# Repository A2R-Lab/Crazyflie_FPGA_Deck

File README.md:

# Deck_FPGA

This repository documents the design of an FPGA-based expansion board for the Crazyflie drone platform, featuring an AMD Xilinx Artix-7 100T FPGA and developed in KiCad.

The board was developed to support the acceleration of linear Model Predictive Control (MPC) execution onboard the Crazyflie quadrotor platform.

## Repository Contents

- `Deck_FPGA.kicad_sch`: KiCad schematic
- `Deck_FPGA.kicad_pcb`: KiCad PCB layout
- `Deck_FPGA.kicad_pro`: KiCad project file
- `Deck_FPGA.pdf`: exported board documentation
- `plot/`: fabrication outputs / Gerbers

## Inspiration

This project was inspired by the board presented in *FPGA-Based Neural Thrust Controller for UAVs* by Sharif Azem, David Scheunert, Mengguang Li, Jonas Gehrunger, Kai Cui, Christian Hochberger, and Heinz Koeppl (2024).

## Related Components

- FPGA accelerator implementation: `ADMM_FPGA`
- Crazyflie firmware integration: `crazyflie_fpga_firmware`

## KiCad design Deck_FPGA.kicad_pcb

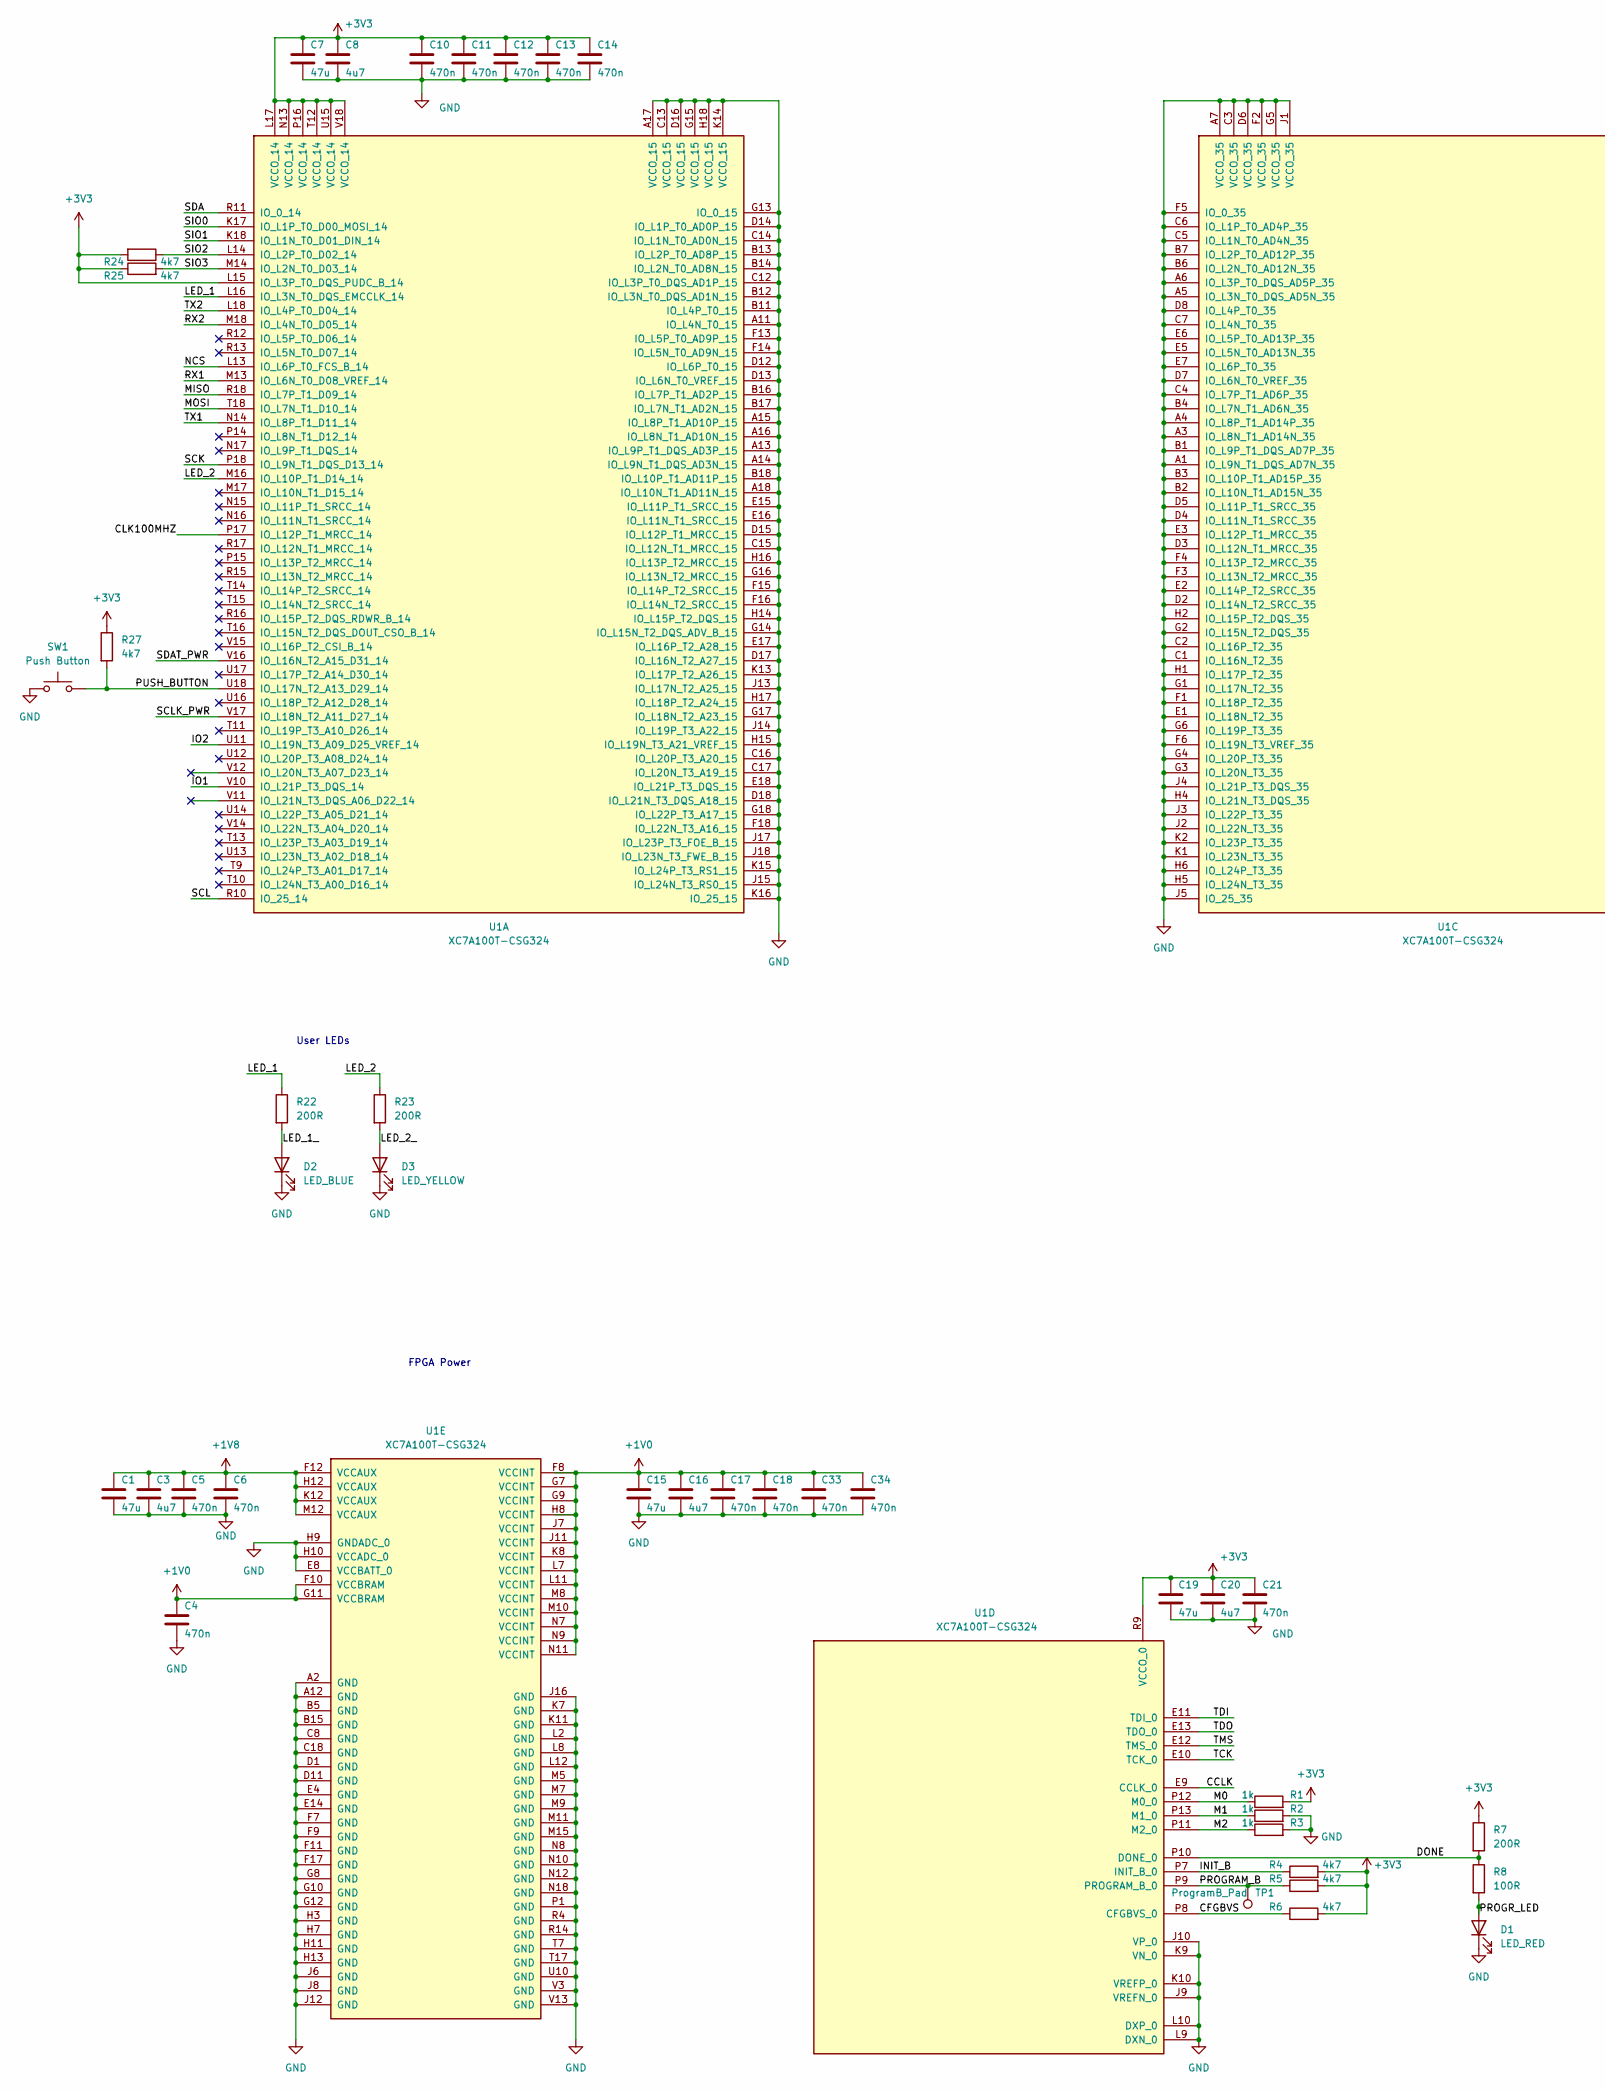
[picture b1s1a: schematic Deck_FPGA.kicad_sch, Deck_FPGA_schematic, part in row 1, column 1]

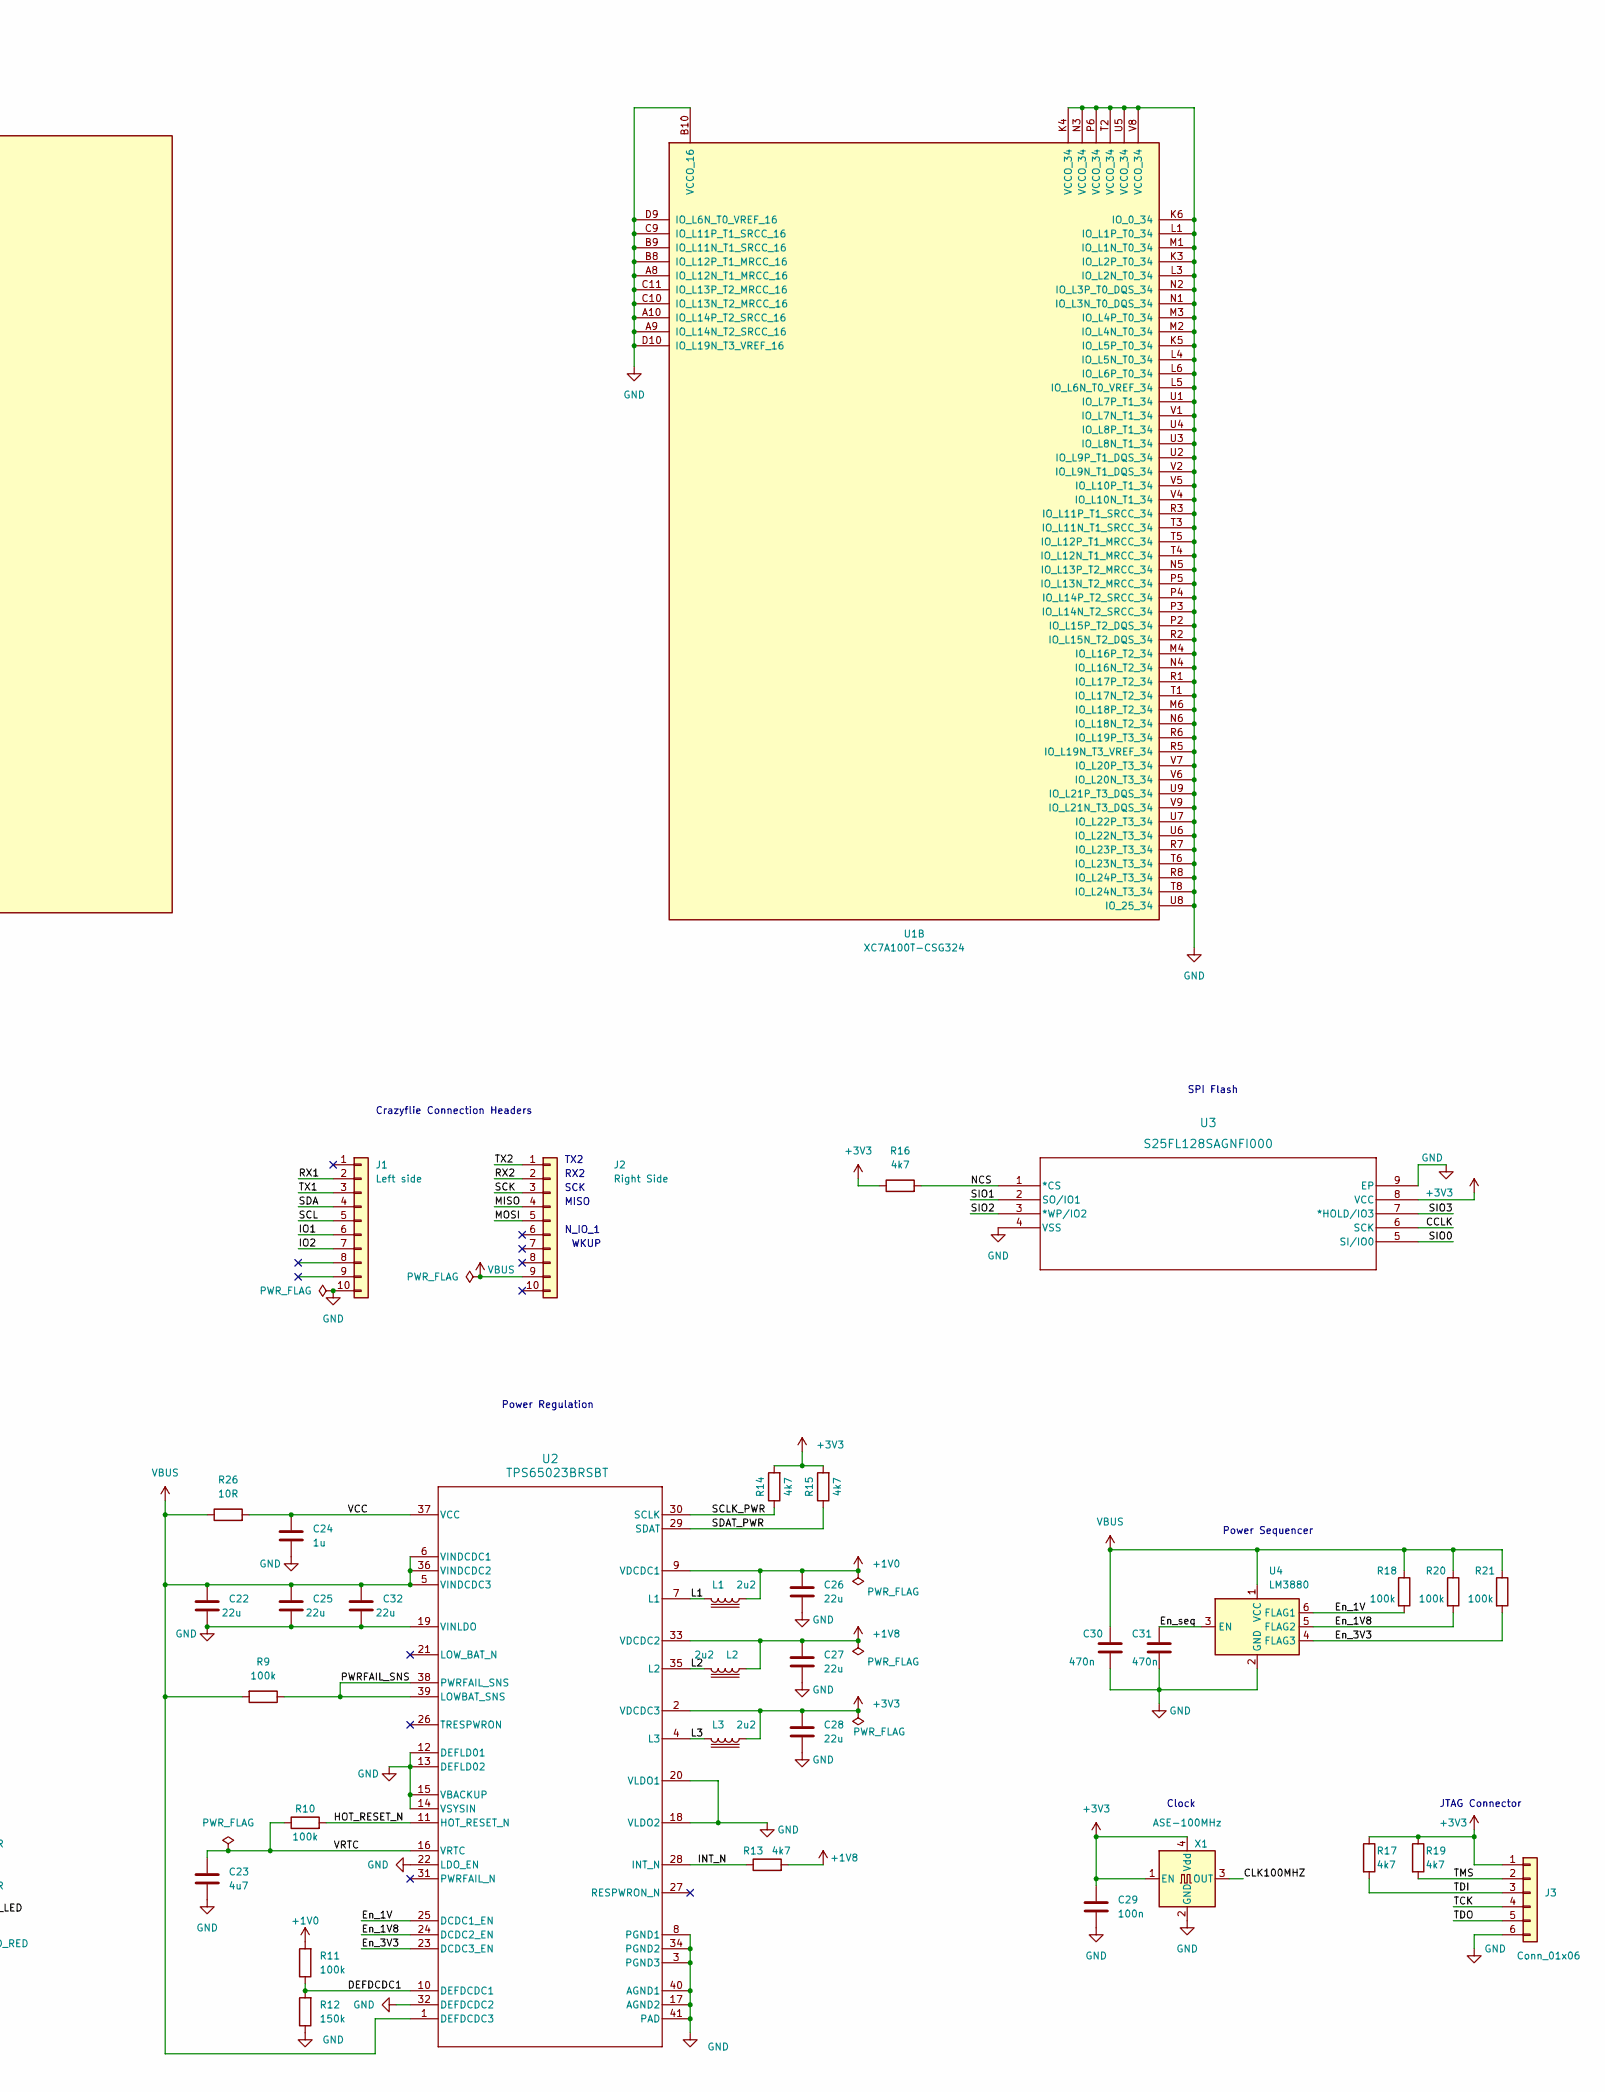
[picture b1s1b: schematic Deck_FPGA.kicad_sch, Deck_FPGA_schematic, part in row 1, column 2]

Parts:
C1: 47u; C_0603_1608Metric; LCSC C140782
C3, C16: 4u7; C_0402_1005Metric; LCSC C23733
C4: 470n; C_0402_1005Metric; LCSC C106255
C5, C6, C10, C11, C12, C13, C14, C17, C18, C21, C30, C31, C33, C34: 470n; C_0402_1005Metric
C7, C15, C19: 47u; C_0603_1608Metric
C8, C20, C23: 4u7; C_0402_1005Metric
C22, C25: 22u; C_0603_1608Metric; LCSC C86295
C24: 1u; C_0603_1608Metric; LCSC C15849
C26, C27, C28, C32: 22u; C_0603_1608Metric
C29: 100n; C_0402_1005Metric; LCSC C60474
D1: LED_RED; LED_0603_1608Metric; LCSC C5879214
D2: LED_BLUE; LED_0603_1608Metric; LCSC C5879217
D3: LED_YELLOW; LED_0603_1608Metric; LCSC C5879216
J1: Left side; BF090-10-X-B2
J2: Right Side; BF090-10-X-B2
J3: Conn_01x06; PinHeader_1x06_P2.54mm_Vertical
L1: 2u2; IND_WE-PMCI_0806_WRE; LCSC C71386
L2, L3: 2u2; IND_WE-PMCI_0806_WRE
R1: 1k; R_0402_1005Metric; LCSC C11702
R2, R3: 1k; R_0402_1005Metric
R4: 4k7; R_0402_1005Metric; LCSC C25900
R5, R6, R13, R14, R15, R16, R17, R19, R24, R25, R27: 4k7; R_0402_1005Metric
R7: 200R; R_0402_1005Metric; LCSC C25087
R8: 100R; R_0402_1005Metric; LCSC C25076
R9: 100k; R_0402_1005Metric; LCSC C2906859
R10, R11, R18, R20, R21: 100k; R_0402_1005Metric
R12: 150k; R_0402_1005Metric; LCSC C2909320
R22, R23: 200R; R_0402_1005Metric
R26: 10R; R_0402_1005Metric; LCSC C413044
SW1: Push Button; SW_EVQ-P3401P; LCSC C79163
TP1: ProgramB_Pad; TestPoint_Pad_D1.0mm
U1: XC7A100T-CSG324; Xilinx_CSG324; LCSC C5181214
U2: TPS65023BRSBT; RSB0040B; LCSC C138723
U3: S25FL128SAGNFI000; WNG008_SPA; LCSC C22445046
U4: LM3880; SOT-23-6; LCSC C2650186
X1: ASE-100MHz; Oscillator_SMD_Abracon_ASE-4Pin_3.2x2.5mm; LCSC C596959

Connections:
+1V0: C4.1, C15.1, C16.1, C17.1, C18.1, C26.1, C33.1, C34.1, L1.1, R11.2, U1.F8 (VCCINT), U1.F10 (VCCBRAM), U1.G7 (VCCINT), U1.G9 (VCCINT), U1.G11 (VCCBRAM), U1.H8 (VCCINT), U1.J7 (VCCINT), U1.J11 (VCCINT), U1.K8 (VCCINT), U1.L7 (VCCINT), U1.L11 (VCCINT), U1.M8 (VCCINT), U1.M10 (VCCINT), U1.N7 (VCCINT), U1.N9 (VCCINT), U1.N11 (VCCINT), U2.9 (VDCDC1)
+1V8: C1.1, C3.1, C5.1, C6.1, C27.1, L2.2, R13.2, U1.F12 (VCCAUX), U1.H12 (VCCAUX), U1.K12 (VCCAUX), U1.M12 (VCCAUX), U2.33 (VDCDC2)
+3V3: C7.1, C8.1, C10.1, C11.1, C12.1, C13.1, C14.1, C19.1, C20.1, C21.1, C28.1, C29.1, J3.1, L3.1, R1.2, R4.2, R5.2, R6.2, R7.1, R14.2, R15.2, R16.1, R17.1, R19.1, R24.2, R25.1, R27.1, U1.L15 (IO_L3P_T0_DQS_PUDC_B_14), U1.L17 (VCCO_14), U1.N13 (VCCO_14), U1.P16 (VCCO_14), U1.R9 (VCCO_0), U1.T12 (VCCO_14), U1.U15 (VCCO_14), U1.V18 (VCCO_14), U2.2 (VDCDC3), U3.8 (VCC), X1.1 (EN), X1.4 (Vdd)
/CCLK: U1.E9 (CCLK_0), U3.6 (SCK)
/CFGBVS: R6.1, U1.P8 (CFGBVS_0)
/CLK100MHZ: U1.P17 (IO_L12P_T1_MRCC_14), X1.3 (OUT)
/DEFDCDC1: R11.1, R12.2, U2.10 (DEFDCDC1)
/DONE: R7.2, R8.1, U1.P10 (DONE_0)
/En_1V: R18.2, U2.25 (DCDC1_EN), U4.6 (FLAG1)
/En_1V8: R20.2, U2.24 (DCDC2_EN), U4.5 (FLAG2)
/En_3V3: R21.2, U2.23 (DCDC3_EN), U4.4 (FLAG3)
/En_seq: C31.1, U4.3 (EN)
/HOT_RESET_N: R10.2, U2.11 (HOT_RESET_N)
/INIT_B: R4.1, U1.P7 (INIT_B_0)
/INT_N: R13.1, U2.28 (INT_N)
/IO1: J1.6, U1.V10 (IO_L21P_T3_DQS_14)
/IO2: J1.7, U1.U11 (IO_L19N_T3_A09_D25_VREF_14)
/L1: L1.2, U2.7 (L1)
/L2: L2.1, U2.35 (L2)
/L3: L3.2, U2.4 (L3)
/LED_1: R22.1, U1.L16 (IO_L3N_T0_DQS_EMCCLK_14)
/LED_1_: D2.2 (A), R22.2
/LED_2: R23.1, U1.M16 (IO_L10P_T1_D14_14)
/LED_2_: D3.2 (A), R23.2
/M0: R1.1, U1.P12 (M0_0)
/M1: R2.1, U1.P13 (M1_0)
/M2: R3.1, U1.P11 (M2_0)
/MISO: J2.4, U1.R18 (IO_L7P_T1_D09_14)
/MOSI: J2.5, U1.T18 (IO_L7N_T1_D10_14)
/NCS: R16.2, U1.L13 (IO_L6P_T0_FCS_B_14), U3.1 (*CS)
/PROGRAM_B: R5.1, TP1.1, U1.P9 (PROGRAM_B_0)
/PROGR_LED: D1.2 (A), R8.2
/PUSH_BUTTON: R27.2, SW1.2, U1.U18 (IO_L17N_T2_A13_D29_14)
/PWRFAIL_SNS: R9.1, U2.38 (PWRFAIL_SNS), U2.39 (LOWBAT_SNS)
/RX1: J1.2, U1.M13 (IO_L6N_T0_D08_VREF_14)
/RX2: J2.2, U1.M18 (IO_L4N_T0_D05_14)
/SCK: J2.3, U1.P18 (IO_L9N_T1_DQS_D13_14)
/SCL: J1.5, U1.R10 (IO_25_14)
/SCLK_PWR: R14.1, U1.V17 (IO_L18N_T2_A11_D27_14), U2.30 (SCLK)
/SDA: J1.4, U1.R11 (IO_0_14)
/SDAT_PWR: R15.1, U1.V16 (IO_L16N_T2_A15_D31_14), U2.29 (SDAT)
/SIO0: U1.K17 (IO_L1P_T0_D00_MOSI_14), U3.5 (SI/IO0)
/SIO1: U1.K18 (IO_L1N_T0_D01_DIN_14), U3.2 (SO/IO1)
/SIO2: R24.1, U1.L14 (IO_L2P_T0_D02_14), U3.3 (*WP/IO2)
/SIO3: R25.2, U1.M14 (IO_L2N_T0_D03_14), U3.7 (*HOLD/IO3)
/TCK: J3.4, U1.E10 (TCK_0)
/TDI: J3.3, R17.2, U1.E11 (TDI_0)
/TDO: J3.5, U1.E13 (TDO_0)
/TMS: J3.2, R19.2, U1.E12 (TMS_0)
/TX1: J1.3, U1.N14 (IO_L8P_T1_D11_14)
/TX2: J2.1, U1.L18 (IO_L4P_T0_D04_14)
/VCC: C24.1, R26.2, U2.37 (VCC)
/VRTC: C23.1, R10.1, U2.16 (VRTC)
GND: C1.2, C3.2, C4.2, C5.2, C6.2, C7.2, C8.2, C10.2, C11.2, C12.2, C13.2, C14.2, C15.2, C16.2, C17.2, C18.2, C19.2, C20.2, C21.2, C22.2, C23.2, C24.2, C25.2, C26.2, C27.2, C28.2, C29.2, C30.2, C31.2, C32.2, C33.2, C34.2, D1.1 (K), D2.1 (K), D3.1 (K), J1.10, J3.6, R2.2, R3.2, R12.1, SW1.1, U1.A1 (IO_L9N_T1_DQS_AD7N_35), U1.A2 (GND), U1.A3 (IO_L8N_T1_AD14N_35), U1.A4 (IO_L8P_T1_AD14P_35), U1.A5 (IO_L3N_T0_DQS_AD5N_35), U1.A6 (IO_L3P_T0_DQS_AD5P_35), U1.A7 (VCCO_35), U1.A8 (IO_L12N_T1_MRCC_16), U1.A9 (IO_L14N_T2_SRCC_16), U1.A10 (IO_L14P_T2_SRCC_16), U1.A11 (IO_L4N_T0_15), U1.A12 (GND), U1.A13 (IO_L9P_T1_DQS_AD3P_15), U1.A14 (IO_L9N_T1_DQS_AD3N_15), U1.A15 (IO_L8P_T1_AD10P_15), U1.A16 (IO_L8N_T1_AD10N_15), U1.A17 (VCCO_15), U1.A18 (IO_L10N_T1_AD11N_15), U1.B1 (IO_L9P_T1_DQS_AD7P_35), U1.B2 (IO_L10N_T1_AD15N_35), U1.B3 (IO_L10P_T1_AD15P_35), U1.B4 (IO_L7N_T1_AD6N_35), U1.B5 (GND), U1.B6 (IO_L2N_T0_AD12N_35), U1.B7 (IO_L2P_T0_AD12P_35), U1.B8 (IO_L12P_T1_MRCC_16), U1.B9 (IO_L11N_T1_SRCC_16), U1.B10 (VCCO_16), U1.B11 (IO_L4P_T0_15), U1.B12 (IO_L3N_T0_DQS_AD1N_15), U1.B13 (IO_L2P_T0_AD8P_15), U1.B14 (IO_L2N_T0_AD8N_15), U1.B15 (GND), U1.B16 (IO_L7P_T1_AD2P_15), U1.B17 (IO_L7N_T1_AD2N_15), U1.B18 (IO_L10P_T1_AD11P_15), U1.C1 (IO_L16N_T2_35), U1.C2 (IO_L16P_T2_35), U1.C3 (VCCO_35), U1.C4 (IO_L7P_T1_AD6P_35), U1.C5 (IO_L1N_T0_AD4N_35), U1.C6 (IO_L1P_T0_AD4P_35), U1.C7 (IO_L4N_T0_35), U1.C8 (GND), U1.C9 (IO_L11P_T1_SRCC_16), U1.C10 (IO_L13N_T2_MRCC_16), U1.C11 (IO_L13P_T2_MRCC_16), U1.C12 (IO_L3P_T0_DQS_AD1P_15), U1.C13 (VCCO_15), U1.C14 (IO_L1N_T0_AD0N_15), U1.C15 (IO_L12N_T1_MRCC_15), U1.C16 (IO_L20P_T3_A20_15), U1.C17 (IO_L20N_T3_A19_15), U1.C18 (GND), U1.D1 (GND), U1.D2 (IO_L14N_T2_SRCC_35), U1.D3 (IO_L12N_T1_MRCC_35), U1.D4 (IO_L11N_T1_SRCC_35), U1.D5 (IO_L11P_T1_SRCC_35), U1.D6 (VCCO_35), U1.D7 (IO_L6N_T0_VREF_35), U1.D8 (IO_L4P_T0_35), U1.D9 (IO_L6N_T0_VREF_16), U1.D10 (IO_L19N_T3_VREF_16), U1.D11 (GND), U1.D12 (IO_L6P_T0_15), U1.D13 (IO_L6N_T0_VREF_15), U1.D14 (IO_L1P_T0_AD0P_15), U1.D15 (IO_L12P_T1_MRCC_15), U1.D16 (VCCO_15), U1.D17 (IO_L16N_T2_A27_15), U1.D18 (IO_L21N_T3_DQS_A18_15), U1.E1 (IO_L18N_T2_35), U1.E2 (IO_L14P_T2_SRCC_35), U1.E3 (IO_L12P_T1_MRCC_35), U1.E4 (GND), U1.E5 (IO_L5N_T0_AD13N_35), U1.E6 (IO_L5P_T0_AD13P_35), U1.E7 (IO_L6P_T0_35), U1.E8 (VCCBATT_0), U1.E14 (GND), U1.E15 (IO_L11P_T1_SRCC_15), U1.E16 (IO_L11N_T1_SRCC_15), U1.E17 (IO_L16P_T2_A28_15), U1.E18 (IO_L21P_T3_DQS_15), U1.F1 (IO_L18P_T2_35), U1.F2 (VCCO_35), U1.F3 (IO_L13N_T2_MRCC_35), U1.F4 (IO_L13P_T2_MRCC_35), U1.F5 (IO_0_35), U1.F6 (IO_L19N_T3_VREF_35), U1.F7 (GND), U1.F9 (GND), U1.F11 (GND), U1.F13 (IO_L5P_T0_AD9P_15), U1.F14 (IO_L5N_T0_AD9N_15), U1.F15 (IO_L14P_T2_SRCC_15), U1.F16 (IO_L14N_T2_SRCC_15), U1.F17 (GND), U1.F18 (IO_L22N_T3_A16_15), U1.G1 (IO_L17N_T2_35), U1.G2 (IO_L15N_T2_DQS_35), U1.G3 (IO_L20N_T3_35), U1.G4 (IO_L20P_T3_35), U1.G5 (VCCO_35), U1.G6 (IO_L19P_T3_35), U1.G8 (GND), U1.G10 (GND), U1.G12 (GND), U1.G13 (IO_0_15), U1.G14 (IO_L15N_T2_DQS_ADV_B_15), U1.G15 (VCCO_15), U1.G16 (IO_L13N_T2_MRCC_15), U1.G17 (IO_L18N_T2_A23_15), U1.G18 (IO_L22P_T3_A17_15), U1.H1 (IO_L17P_T2_35), U1.H2 (IO_L15P_T2_DQS_35), U1.H3 (GND), U1.H4 (IO_L21N_T3_DQS_35), U1.H5 (IO_L24N_T3_35), U1.H6 (IO_L24P_T3_35), U1.H7 (GND), U1.H9 (GNDADC_0), U1.H10 (VCCADC_0), U1.H11 (GND), U1.H13 (GND), U1.H14 (IO_L15P_T2_DQS_15), U1.H15 (IO_L19N_T3_A21_VREF_15), U1.H16 (IO_L13P_T2_MRCC_15), U1.H17 (IO_L18P_T2_A24_15), U1.H18 (VCCO_15), U1.J1 (VCCO_35), U1.J2 (IO_L22N_T3_35), U1.J3 (IO_L22P_T3_35), U1.J4 (IO_L21P_T3_DQS_35), U1.J5 (IO_25_35), U1.J6 (GND), U1.J8 (GND), U1.J9 (VREFN_0), U1.J10 (VP_0), U1.J12 (GND), U1.J13 (IO_L17N_T2_A25_15), U1.J14 (IO_L19P_T3_A22_15), U1.J15 (IO_L24N_T3_RS0_15), U1.J16 (GND), U1.J17 (IO_L23P_T3_FOE_B_15), U1.J18 (IO_L23N_T3_FWE_B_15), U1.K1 (IO_L23N_T3_35), U1.K2 (IO_L23P_T3_35), U1.K3 (IO_L2P_T0_34), U1.K4 (VCCO_34), U1.K5 (IO_L5P_T0_34), U1.K6 (IO_0_34), U1.K7 (GND), U1.K9 (VN_0), U1.K10 (VREFP_0), U1.K11 (GND), U1.K13 (IO_L17P_T2_A26_15), U1.K14 (VCCO_15), U1.K15 (IO_L24P_T3_RS1_15), U1.K16 (IO_25_15), U1.L1 (IO_L1P_T0_34), U1.L2 (GND), U1.L3 (IO_L2N_T0_34), U1.L4 (IO_L5N_T0_34), U1.L5 (IO_L6N_T0_VREF_34), U1.L6 (IO_L6P_T0_34), U1.L8 (GND), U1.L9 (DXN_0), U1.L10 (DXP_0), U1.L12 (GND), U1.M1 (IO_L1N_T0_34), U1.M2 (IO_L4N_T0_34), U1.M3 (IO_L4P_T0_34), U1.M4 (IO_L16P_T2_34), U1.M5 (GND), U1.M6 (IO_L18P_T2_34), U1.M7 (GND), U1.M9 (GND), U1.M11 (GND), U1.M15 (GND), U1.N1 (IO_L3N_T0_DQS_34), U1.N2 (IO_L3P_T0_DQS_34), U1.N3 (VCCO_34), U1.N4 (IO_L16N_T2_34), U1.N5 (IO_L13P_T2_MRCC_34), U1.N6 (IO_L18N_T2_34), U1.N8 (GND), U1.N10 (GND), U1.N12 (GND), U1.N18 (GND), U1.P1 (GND), U1.P2 (IO_L15P_T2_DQS_34), U1.P3 (IO_L14N_T2_SRCC_34), U1.P4 (IO_L14P_T2_SRCC_34), U1.P5 (IO_L13N_T2_MRCC_34), U1.P6 (VCCO_34), U1.R1 (IO_L17P_T2_34), U1.R2 (IO_L15N_T2_DQS_34), U1.R3 (IO_L11P_T1_SRCC_34), U1.R4 (GND), U1.R5 (IO_L19N_T3_VREF_34), U1.R6 (IO_L19P_T3_34), U1.R7 (IO_L23P_T3_34), U1.R8 (IO_L24P_T3_34), U1.R14 (GND), U1.T1 (IO_L17N_T2_34), U1.T2 (VCCO_34), U1.T3 (IO_L11N_T1_SRCC_34), U1.T4 (IO_L12N_T1_MRCC_34), U1.T5 (IO_L12P_T1_MRCC_34), U1.T6 (IO_L23N_T3_34), U1.T7 (GND), U1.T8 (IO_L24N_T3_34), U1.T17 (GND), U1.U1 (IO_L7P_T1_34), U1.U2 (IO_L9P_T1_DQS_34), U1.U3 (IO_L8N_T1_34), U1.U4 (IO_L8P_T1_34), U1.U5 (VCCO_34), U1.U6 (IO_L22N_T3_34), U1.U7 (IO_L22P_T3_34), U1.U8 (IO_25_34), U1.U9 (IO_L21P_T3_DQS_34), U1.U10 (GND), U1.V1 (IO_L7N_T1_34), U1.V2 (IO_L9N_T1_DQS_34), U1.V3 (GND), U1.V4 (IO_L10N_T1_34), U1.V5 (IO_L10P_T1_34), U1.V6 (IO_L20N_T3_34), U1.V7 (IO_L20P_T3_34), U1.V8 (VCCO_34), U1.V9 (IO_L21N_T3_DQS_34), U1.V13 (GND), U2.3 (PGND3), U2.8 (PGND1), U2.12 (DEFLD01), U2.13 (DEFLD02), U2.14 (VSYSIN), U2.15 (VBACKUP), U2.17 (AGND2), U2.18 (VLDO2), U2.19 (VINLDO), U2.20 (VLDO1), U2.22 (LDO_EN), U2.32 (DEFDCDC2), U2.34 (PGND2), U2.40 (AGND1), U2.41 (PAD), U3.4 (VSS), U3.9 (EP), U4.2 (GND), X1.2 (GND)
VBUS: C22.1, C25.1, C30.1, C32.1, J2.9, R9.2, R18.1, R20.1, R21.1, R26.1, U2.1 (DEFDCDC3), U2.5 (VINDCDC3), U2.6 (VINDCDC1), U2.36 (VINDCDC2), U4.1 (VCC)

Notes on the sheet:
RX2
TX2
User LEDs
Power Regulation
MISO
SCK
Crazyflie Connection Headers
FPGA Power
Clock
Power Sequencer
N_IO_1
JTAG Connector
WKUP
SPI Flash

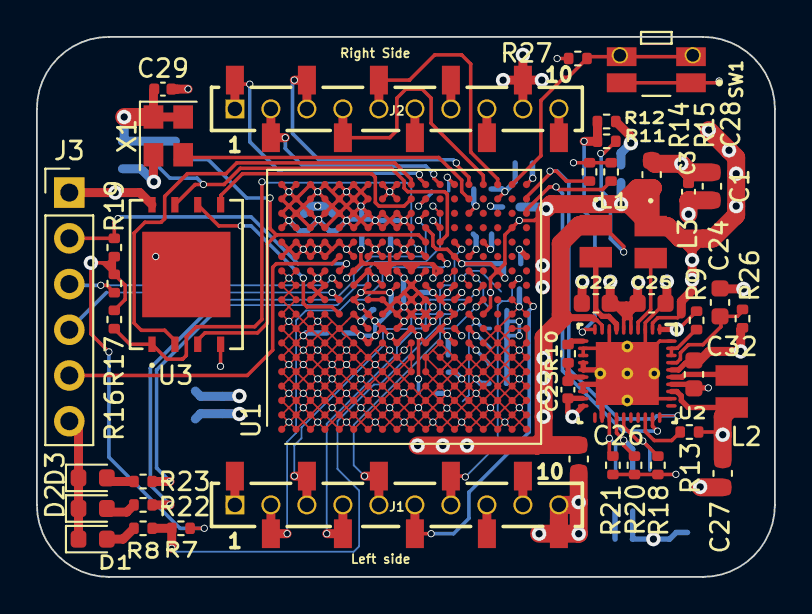
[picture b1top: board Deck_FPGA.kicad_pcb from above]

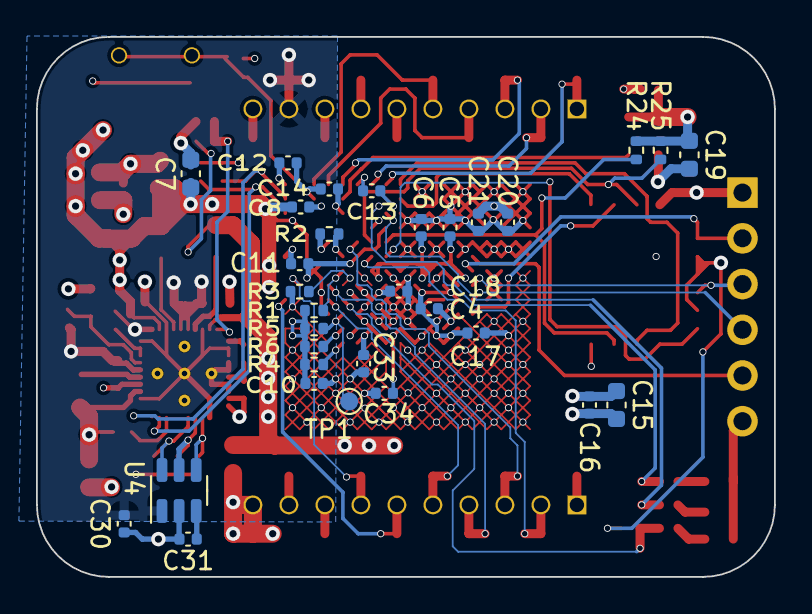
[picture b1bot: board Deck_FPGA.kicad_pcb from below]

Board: 4 copper layers, 41.0 x 30.0 mm, 75 parts (31 on the bottom side), 55 nets.

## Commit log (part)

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2026-03-12 readme
2026-03-12 license
